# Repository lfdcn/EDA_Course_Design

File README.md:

# EDA课设

> 大三刚开学就两次连续的课设，很难受，感觉课太多，不过这次EDA课设算是个福利，但是没学到什么东西……有两道题目，第一道是使用以前的数电知识完成的，没什么兴趣，第二个使用单片机，看下题目

```reStructuredText
题目二  温湿度采集器设计
本设计要求利用Proteus设计软件进行设计开发，运用单片机设计一个具有温湿度采集和显示功能的电路，并实现其仿真运行调试。最后通过查找相关器件的封装资料，把设计的电路在AD软件上画出原理图，封装库以及完整的PCB图。
功能简介
1.	实现学号（根据自己的完整学号）显示在LED数码管显示（或液晶），启动后显示本人学号
2.	实现温度，湿度的采集，并实时显示在液晶上。
3.	当温度高于35时，点亮一个绿色LED灯，当湿度高于55时，点亮一个黄色LED灯。当两者都高于限值时，点亮红色LED灯，并且蜂鸣器响起。
评分标准
所有学生必须实现以上所有功能并且画出原理图和PCB图，否者考评为“不及格”。在此基础上，将根据元器件布局、连接线分布是否合理、美观进行30分以内的加分。自行设计添加其他功能，将根据功能的实现难度及实用性另外进行10分以内的。
```

## 仿真&&代码

​	咋一看这个题目就想着用32去解决，但发现居然不熟悉Proteus，自己也因为做项目的原因，用的eclipse+C++的环境居然十分不熟悉，想着用RT-Thread Studio解决发现Proteus仿真居然出错！！！真的是X了！51单片机又太古老，已经一年多没去写过寄存器了，不想弄，毕竟大多数人做这个题目都是弄51，没意思呐！

​	看下Proteus还有什么芯片可以用，偶然间发现了Arduino！！！这不是更简单吗？开始写程序！！！

``` c++
#include <SerLCD.h>
#include <Wire.h>
#include <DHT.h>
#include <DHT_U.h>

#define DHTPin 7
#define LCDPin 8
#define GREEN 13
#define YELLOW 12
#define RED 11
#define BUZZER 10

DHT dht(DHTPin,DHT11);
SerLCD lcd;
//int i = 0;
// the setup function runs once when you press reset or power the board
void setup() {
  // initialize digital pin LED_BUILTIN as an output.
  Serial.begin(9600);
  dht.begin(); //DHT开始工作
  lcd.begin(Serial);

  lcd.setBacklight(255,255,255);
  lcd.setContrast(5);
  lcd.clear();
  
  pinMode(GREEN, OUTPUT);
  pinMode(YELLOW, OUTPUT);
  pinMode(RED, OUTPUT);
  Serial.print("201810224113");
  delay(2000);
}

// the loop function runs over and over again forever
void loop() {
  float h = dht.readHumidity();//读湿度
  float t = dht.readTemperature();//读温度，默认为摄氏度

  adjust(h,t);
  display(h,t);
}

void display(int h,int t)
{
  lcd.setCursor(0, 0);
  lcd.print("NO.201810224113");
  lcd.setCursor(0,1);
  lcd.print("Temperature:");
  lcd.setCursor(12,1);
  lcd.print(t);
  lcd.setCursor(0,2);
  lcd.print("Humidity:");
  lcd.setCursor(9,2);
  lcd.print(h);
  lcd.setCursor(0,3);
  lcd.print("Designed by:lfdcn");
}

void adjust(int h,int t)
{
    if(t>35&&h>55)
  {
    digitalWrite(GREEN,LOW);
    digitalWrite(YELLOW,LOW);
    digitalWrite(RED,HIGH);
    digitalWrite(BUZZER,HIGH);
  }
  else if(t>35)
  {
    digitalWrite(GREEN,HIGH);
    digitalWrite(RED,LOW);
    digitalWrite(YELLOW,LOW);
    digitalWrite(BUZZER,LOW);
  }
  else if(h>55)
  {
    digitalWrite(YELLOW,HIGH);
    digitalWrite(GREEN,LOW);
    digitalWrite(RED,LOW);
    digitalWrite(BUZZER,LOW);
  }
  else
  {
    digitalWrite(GREEN,LOW);
    digitalWrite(YELLOW,LOW);
    digitalWrite(RED,LOW);
    digitalWrite(BUZZER,LOW);
  }
}
```

这里其实有更好的方式去优化下代码，不至于看上去这么地肿……但是考虑到时间和我多年没写代码地原因，理解下，哈哈！！！、

**注释？这点代码还注释？？？**

这个用了DHT的库以及一个串口屏的库，这不是送分题吗？看下代码多方便，代码写得都不用1个钟（要配合电路设计），在看下我的Proteus的电路设计：

简单吧？Arduino的威力！以后万一要使用STM32、HC32、GD32什么的，直接移植它们的库啊！

## PCB设计

> 老本行了，本来都不想走硬件路线的，懂我的都懂……无敌的kicad

### 原理图设计

这个是用以前画的Arduino的板子修改来的，得心应手，一边回复小班的信息一边修改，还是蛮简单的，还加入了下载CH340电路，简直不要太好画！哦！不，就主要是删除之前的一些电机，一些接口，一些无线什么的功能而已！

### PCB设计

卧槽，咋一看这个布局怎么这么丑陋！好吧说实话是随便布的，就像J哥说的，这种频率的板子，怎么布不都一样？？？除了差分线注意一下，其它没什么注意的，毕竟之前画过这板子！哈哈！

什么？嫌丑？kicad没有自动布线，虽然丑，好歹也是自动布线的，老罗的板子还没完成呢，这个不管了，时间宝贵！写这篇Blog是为了聪哥

看下3D图吧：

看着可以吗兄弟们，用Arduino是投机取巧的办法，哈哈，过了就好，先过了再说！迟点再优化一下！

## 后续

有可能加入时钟的功能吧，懒得弄了，随便交差再说！睡觉！

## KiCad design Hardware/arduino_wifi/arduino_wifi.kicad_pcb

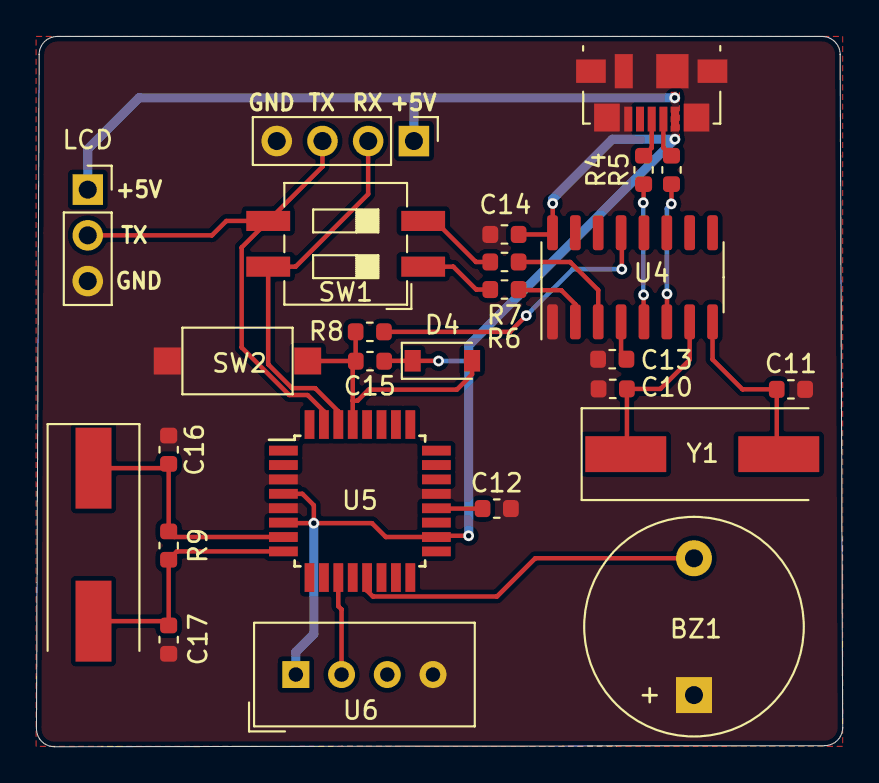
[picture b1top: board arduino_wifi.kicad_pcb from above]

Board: 2 copper layers, 44.8 x 39.5 mm, 26 parts (0 on the bottom side), 22 nets.

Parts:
BZ1: Buzzer; Buzzer_12x9.5RM7.6
C10, C11: 33pF; C_0603_1608Metric
C12, C13, C14, C15: 0.1μF; C_0603_1608Metric
C16, C17: 22pF; C_0603_1608Metric
D4: 1N4148; D_SOD-123
J2: USB_B_Micro; USB_Micro-B_Molex_47346-0001
J4: Conn_01x04_Male; PinHeader_1x04_P2.54mm_Vertical
LCD: LCD; PinSocket_1x03_P2.54mm_Vertical
R4, R5: 22; R_0603_1608Metric
R6, R7: 1K; R_0603_1608Metric
R8: 10K; R_0603_1608Metric
R9: 1M; R_0603_1608Metric
SW1: ATMEL; SW_DIP_SPSTx02_Slide_6.7x6.64mm_W8.61mm_P2.54mm_LowProfile
SW2: MCU_RESET; SW_SPST_CK_RS282G05A3
U4: CH340G; SOIC-16_3.9x9.9mm_P1.27mm
U5: ATmega328-AU; TQFP-32_7x7mm_P0.8mm
U6: DHT11; Aosong_DHT11_5.5x12.0_P2.54mm
Y1: 12Mhz; Crystal_SMD_HC49-SD
Y2: 16Mhz; Crystal_SMD_HC49-SD

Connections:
+5V: C14.2, D4.1, J2.1, J4.1, LCD.1, R8.2, U4.16, U5.4, U5.6, U5.18, U6.1
/AREF: C12.1, U5.20
/DTR: C15.1, U4.13
/MCU_RESET: C15.2, D4.2, R8.1, SW2.1, U5.29
/MRX: J4.2, SW1.4, U5.30
/MTX: J4.3, LCD.2, SW1.3, U5.31
/PB1: BZ1.2, U5.13
/PD7: U5.11, U6.2
GND: BZ1.1, C10.2, C11.2, C12.2, C13.2, C14.1, C16.1, C17.1, J2.5, J2.6, J4.4, LCD.3, SW2.2, U4.1, U5.3, U5.5, U5.21, U6.4
unnamed: C10.1, U4.7, Y1.1
unnamed: C11.1, U4.8, Y1.2
unnamed: C13.1, U4.4
unnamed: C16.2, R9.2, U5.7, Y2.1
unnamed: C17.2, R9.1, U5.8, Y2.2
unnamed: J2.2, R5.2
unnamed: J2.3, R4.2
unnamed: R4.1, U4.5
unnamed: R5.1, U4.6
unnamed: R6.1, SW1.1
unnamed: R6.2, U4.2
unnamed: R7.1, SW1.2
unnamed: R7.2, U4.3

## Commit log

2020-10-25 main
